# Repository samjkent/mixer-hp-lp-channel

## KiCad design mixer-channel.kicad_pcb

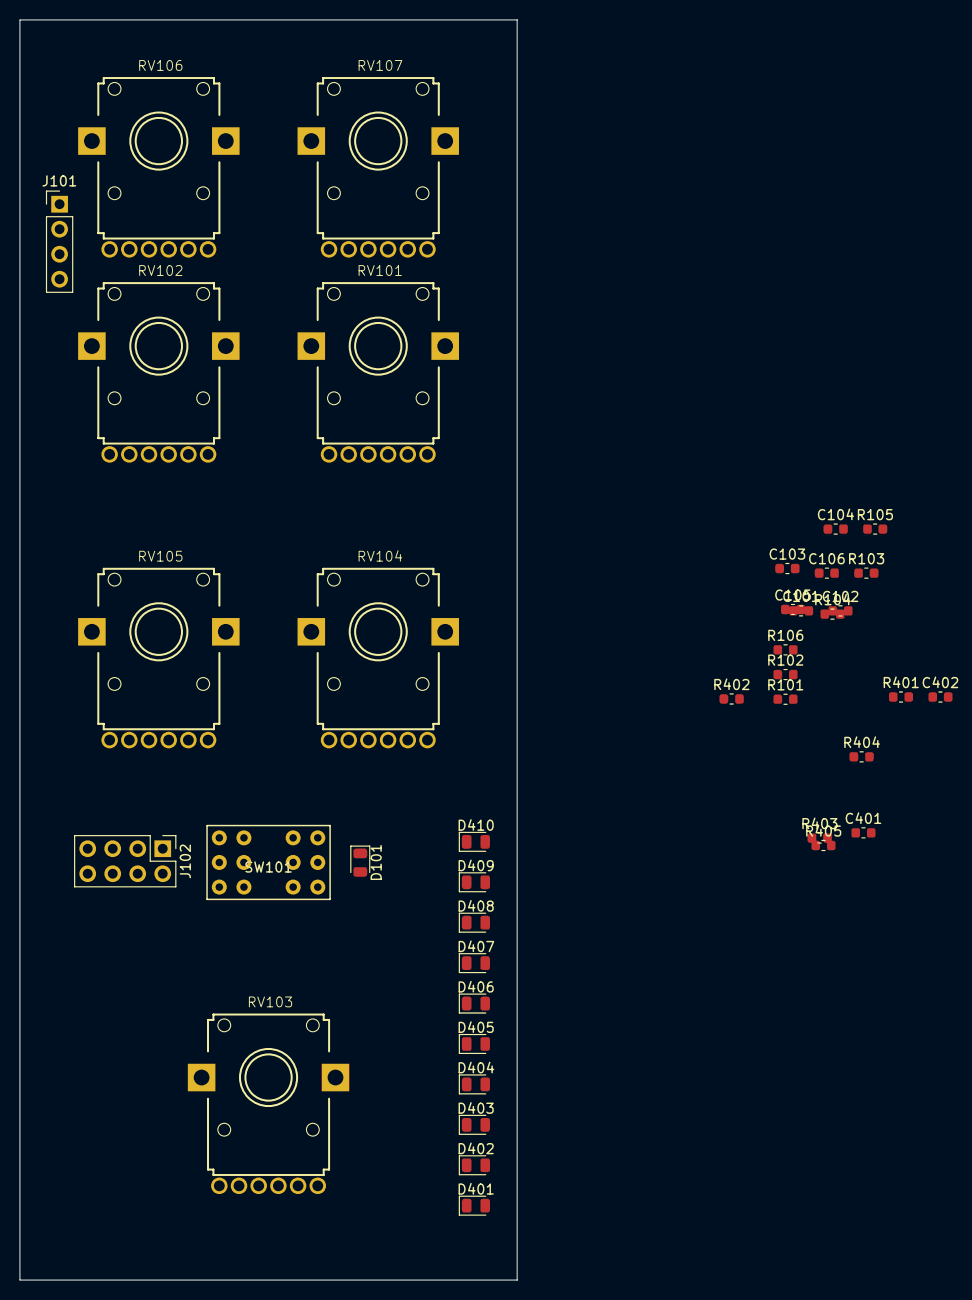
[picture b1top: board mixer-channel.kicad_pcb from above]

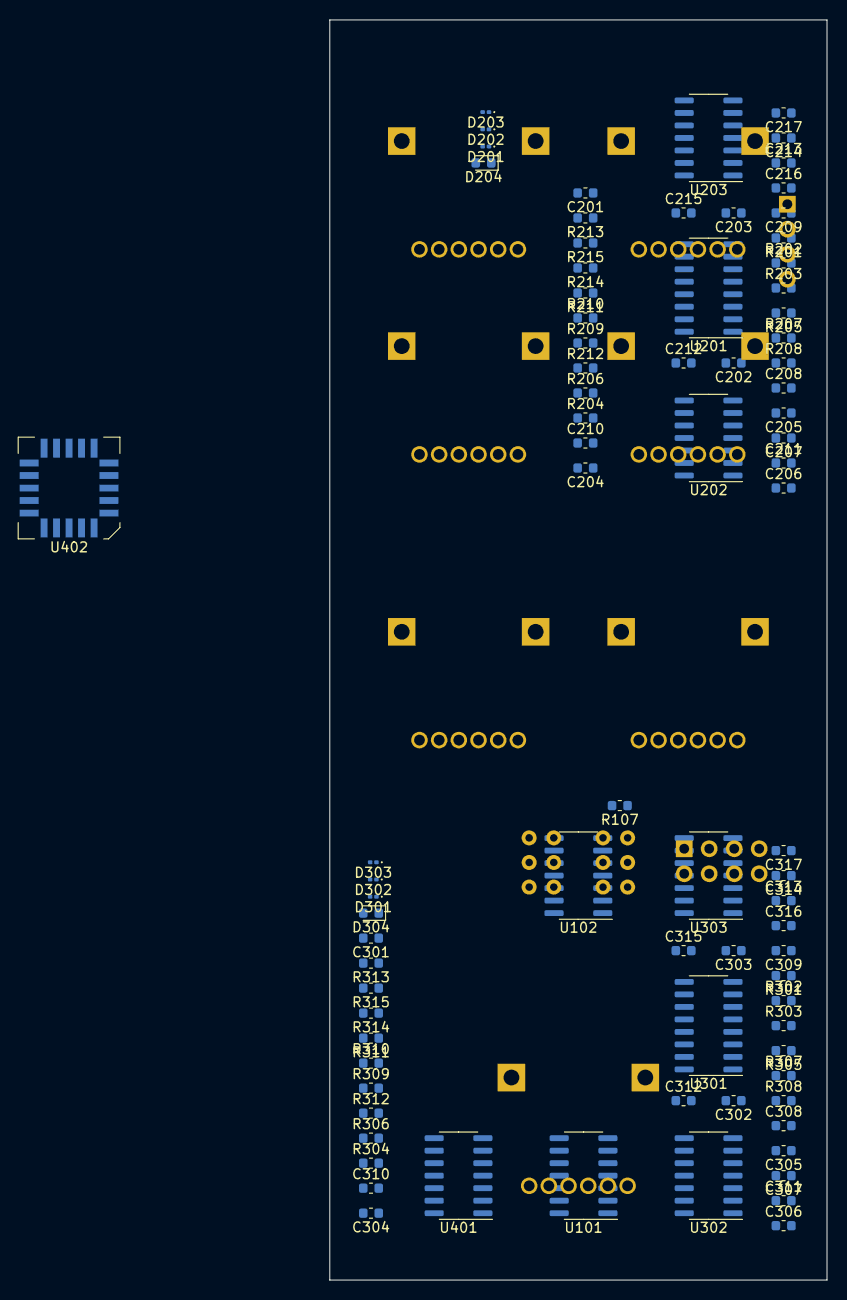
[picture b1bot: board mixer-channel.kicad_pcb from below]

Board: 2 copper layers, 50.5 x 128.0 mm, 123 parts (83 on the bottom side), 94 nets, no tracks yet.

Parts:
C101, C102, C103, C104, C105, C106: C; C_0603_1608Metric
C201, C206, C207, C209, C210, C301, C306, C307, C309, C310: 0.1u; C_0603_1608Metric
C202, C302, C401, C402: 0.1uF; C_0603_1608Metric
C203, C208, C212, C213, C215, C303, C308, C312, C313, C315: 1200p; C_0603_1608Metric
C204, C205, C211, C214, C216, C217, C304, C305, C311, C314, C316, C317: 470p; C_0603_1608Metric
D101, D401, D402, D403, D404, D405, D406, D407, D408, D409, D410: LED; LED_0805_2012Metric
D201, D202, D203, D301, D302, D303: D_Zener; D_0201_0603Metric
D204, D304: D_Zener; D_0603_1608Metric
J101: Conn_01x04_Male; PinHeader_1x04_P2.54mm_Vertical
J102: Conn_02x04_Counter_Clockwise; PinHeader_2x04_P2.54mm_Vertical
R101, R102, R103, R104, R105, R106: R; R_0603_1608Metric
R107, R202, R207, R210, R214, R302, R307, R310, R314: 220; R_0603_1608Metric
R201, R203, R205, R208, R209, R211, R215, R301, R303, R305, R308, R309, R311, R315: 15k; R_0603_1608Metric
R204, R212, R304, R312, R401, R402, R403: 10k; R_0603_1608Metric
R206, R213, R306, R313: 1.8k; R_0603_1608Metric
R404: 1.2k; R_0603_1608Metric
R405: 7.5k; R_0603_1608Metric
RV101: LP_Res; PTV112
RV102: HP_Res; PTV112
RV103: FADER; PTV112
RV104: LP_Fc; PTV112
RV105: HP_Fc; PTV112
RV106: INPUT_GAIN; PTV112
RV107: SEND; PTV112
SW101: SW_4PDT_x4; MHPS4284
U101, U102, U202, U203, U302, U303, U401: TL074; SOIC-14_3.9x8.7mm_P1.27mm
U201, U301: SSI2164; SOIC-16_3.9x9.9mm_P1.27mm
U402: LM3916; PLCC-20

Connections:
+5V: J101.3, RV104.3, RV104.6, RV105.3, RV105.6, SW101.2
/Filter/HP_IN: C211.1, C213.2, R208.1, RV101.6, U202.7
/Filter/HP_RES_WIPER: RV102.5, U203.10
/Filter/LP_RES_WIPER: RV101.5, U202.10
/Filter/VCA1_IN: R201.1, R202.2, R203.2, U201.2
/Filter/VCA1_OUT: C204.1, C205.2, U201.4, U202.2
/Filter/VCA2_IN: R205.1, R207.2, R208.2, U201.7
/Filter/VCA2_OUT: C211.2, U201.5, U202.6
/Filter/VCA3_IN: R209.1, R210.1, R211.2, U201.10
/Filter/VCA3_OUT: C213.1, C214.2, U201.12, U203.2
/Filter/VCA4_IN: R214.1, R215.2, U201.15
/Filter/VCA4_OUT: C216.1, C217.2, U201.13, U203.6
/HP_1: RV105.2, U301.11, U301.14
/HP_2: RV105.5, U201.11, U201.14
/HP_OUT_R: J102.6, SW101.6
/INPUT_L: C103.2, J102.2
/INPUT_R: C104.2, J102.7
/L: R301.2, RV106.3, U102.1
/LP_1: RV104.2, U301.3, U301.6
/LP_2: RV104.5, U201.3, U201.6
/L_PF: RV103.5, U102.5
/OUTPUT_L: J102.1, U102.6, U102.7
/OUTPUT_R: J102.8, U102.13, U102.14
/R: R201.2, RV106.6, U102.8
/R_PF: RV103.2, U102.12
/SEND_OUT_L: J102.4, RV107.2
/SEND_OUT_R: J102.5, RV107.5
/VU_L: C317.1, R315.1, RV102.1, RV103.6, U101.3, U101.10, U303.7, U401.3
/VU_R: C217.1, R215.1, RV102.6, RV103.1, U101.5, U101.12, U203.7, U401.5
/sheet6035AD8F/HP_IN: C311.1, C313.2, R308.1, RV101.1, U302.7
/sheet6035AD8F/HP_RES_WIPER: RV102.2, U303.10
/sheet6035AD8F/LP_RES_WIPER: RV101.2, U302.10
/sheet6035AD8F/VCA1_IN: R301.1, R302.2, R303.2, U301.2
/sheet6035AD8F/VCA1_OUT: C304.1, C305.2, U301.4, U302.2
/sheet6035AD8F/VCA2_IN: R305.1, R307.2, R308.2, U301.7
/sheet6035AD8F/VCA2_OUT: C311.2, U301.5, U302.6
/sheet6035AD8F/VCA3_IN: R309.1, R310.1, R311.2, U301.10
/sheet6035AD8F/VCA3_OUT: C313.1, C314.2, U301.12, U303.2
/sheet6035AD8F/VCA4_IN: R314.1, R315.2, U301.15
/sheet6035AD8F/VCA4_OUT: C316.1, C317.2, U301.13, U303.6
GND: C101.1, C102.1, C105.1, C106.1, C201.2, C202.1, C203.2, C206.2, C207.2, C208.2, C209.2, C210.1, C212.2, C215.2, C301.2, C302.1, C303.2, C306.2, C307.2, C308.2, C309.2, C310.1, C312.2, C315.2, C401.1, C402.1, D101.1, J101.4, R101.2, R102.1, R206.1, R213.1, R306.1, R313.1, R405.2, RV101.3, RV101.4, RV102.3, RV102.4, RV103.3, RV103.4, RV104.1, RV104.4, RV105.1, RV105.4, RV107.1, RV107.4, U102.3, U102.10, U201.8, U202.3, U202.5, U203.3, U203.5, U301.8, U302.3, U302.5, U303.3, U303.5, U401.10, U402.2, U402.4
unnamed: C103.1, R101.1, R103.2
unnamed: C104.1, R102.2, R104.2
unnamed: C203.1, R202.1
unnamed: C204.2, D201.2, R204.2, U202.8
unnamed: C205.1, R203.1, R205.2, U202.1
unnamed: C208.1, R207.1
unnamed: C212.1, R210.2
unnamed: C214.1, C216.2, R211.1, U203.1
unnamed: C215.1, R214.2
unnamed: C303.1, R302.1
unnamed: C304.2, D301.2, R304.2, U302.8
unnamed: C305.1, R303.1, R305.2, U302.1
unnamed: C308.1, R307.1
unnamed: C312.1, R310.2
unnamed: C314.1, C316.2, R311.1, U303.1
unnamed: C315.1, R314.2
unnamed: D101.2, R107.1
unnamed: D201.1, D202.1
unnamed: D202.2, R204.1, R206.2, U202.9
unnamed: D203.1, D204.1
unnamed: D203.2, R209.2, R212.2, U203.8
unnamed: D204.2, R212.1, R213.2, U203.9
unnamed: D301.1, D302.1
unnamed: D302.2, R304.1, R306.2, U302.9
unnamed: D303.1, D304.1
unnamed: D303.2, R309.2, R312.2, U303.8
unnamed: D304.2, R312.1, R313.2, U303.9
unnamed: D401.1, U402.1
unnamed: D401.2, D402.2, D403.2, D404.2, D405.2, D406.2, D407.2, D408.2, D409.2, D410.2
unnamed: D402.1, U402.18
unnamed: D403.1, U402.17
unnamed: D404.1, U402.15
unnamed: D406.1, U402.14
unnamed: D407.1, U402.13
unnamed: D408.1, U402.12
unnamed: D409.1, U402.11
unnamed: D410.1, U402.10
unnamed: R103.1, R105.2, U102.2
unnamed: R104.1, R106.2, U102.9
unnamed: R105.1, RV106.2
unnamed: R106.1, RV106.5
unnamed: R401.1, R402.1, R403.2, U401.9
unnamed: R401.2, U401.1, U401.2
unnamed: R402.2, U401.6, U401.7
unnamed: R403.1, U401.8, U402.5
unnamed: R404.1, U402.6, U402.7
unnamed: R404.2, R405.1, U402.8
unnamed: RV107.3, U101.8, U101.9
unnamed: RV107.6, U101.13, U101.14
unnamed: U101.1, U101.2
unnamed: SW101.5, U101.6, U101.7
VDD: C101.2, C105.2, C201.1, C206.1, C209.1, C301.1, C306.1, C309.1, C401.2, J101.1, U101.4, U102.4, U201.16, U202.4, U203.4, U301.16, U302.4, U303.4, U401.4, U402.3
VSS: C102.2, C106.2, C202.2, C207.1, C210.2, C302.2, C307.1, C310.2, C402.2, J101.2, U101.11, U102.11, U201.9, U202.11, U203.11, U301.9, U302.11, U303.11, U401.11

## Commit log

2021-02-18 Initial commit: untested hardware
